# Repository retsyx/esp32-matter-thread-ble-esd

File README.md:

# Matter Over Thread End Sleepy Device With BLE Commissioning

Implements a motion sensor with an ESP32 and a BMA400 IMU - be notified when the mailman delivers your mail by attaching an accelerometer to the mailbox lid. This code puts together all the bits that seem to be required for a Matter over Thread End Sleepy Device (ESD) with BLE commissioning.

## Power Consumption

This setup seems to average 650µA at 4V from the battery when idling. Detected motion spikes power consumption considerably. The ESP32-C6's idle power draw is very high and not practical for long lived, battery powered, Matter devices.

## Requirements

* An Espressif ESP32 device with a Thread and BLE radio (for example, the ESP32-C6). If using a battery, the device should ideally have a charging circuit to allow charging the LiPo that will power the device. [The SparkFun Qwiic Pocket Development Board](https://www.sparkfun.com/products/22925) has an onboard charger, and is easy to interface with a suitable accelerometer.
* Bosch BMA400 accelerometer. The [SparkFun BMA400 Qwicc board](https://www.sparkfun.com/products/21207) interfaces easily with the SparkFun Qwiic Pocket.
* LiPo Battery. If using the linked SparkFun board, use a battery with a JST PH 2.0mm connector. Ensure that the polarity of the battery leads match the polarity of the board connector. The SparkFun Qwicc Pocket's connector polarity is the opposite of most hobby LiPos sold. Battery connector pins can be easily pried out with a utility knife to reverse their position in the connector.

### Custom Board

Alternatively, an untested custom PCB design based on the XIAO ESP32-C6 and the BMA400 accelerometer is [available](hw/board).

The LiPo Battery JST PH 2.0mm connector polarity for this board matches the typically available LiPo polarity.

## Building

* Install [esp-idf](https://docs.espressif.com/projects/esp-idf/en/stable/esp32/index.html) and [esp-matter](https://docs.espressif.com/projects/esp-matter/en/latest/esp32/)
* Set the target.
    * For the Sparkfun board use esp32-c6.
    * For the custom board, enable **Example Configuration → Use the XIAO ESP32-C6 carrier board** in (`idf.py menuconfig` (`CONFIG_BOARD_XIAO_ESP32C6=y`).
* Build the project, and flash to device

## Commissioning

With your favorite Matter commissioner (HomeKit, etc.) add the accessory.

This project uses development commissioning credentials, so the QR code is always the one below.

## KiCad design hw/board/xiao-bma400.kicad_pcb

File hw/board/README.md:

# XIAO ESP32-C6 / BMA400 Board

**This board has not been manufactured or tested.**

It is a simple board designed in KiCad.

## Manufacturing

It is a standard 2-layer, 1.6mm FR4 board. Dimensions are 40mm x 32mm.

Manufacturing files are available [here](mfr/).

An example BOM is available [here](mfr/bom.csv).

## Building the Firmware

From the repository root, set the ESP-IDF target to `esp32c6`, then enable **Example Configuration → Use the XIAO ESP32-C6 carrier board** in `idf.py menuconfig` (`CONFIG_BOARD_XIAO_ESP32C6=y`).

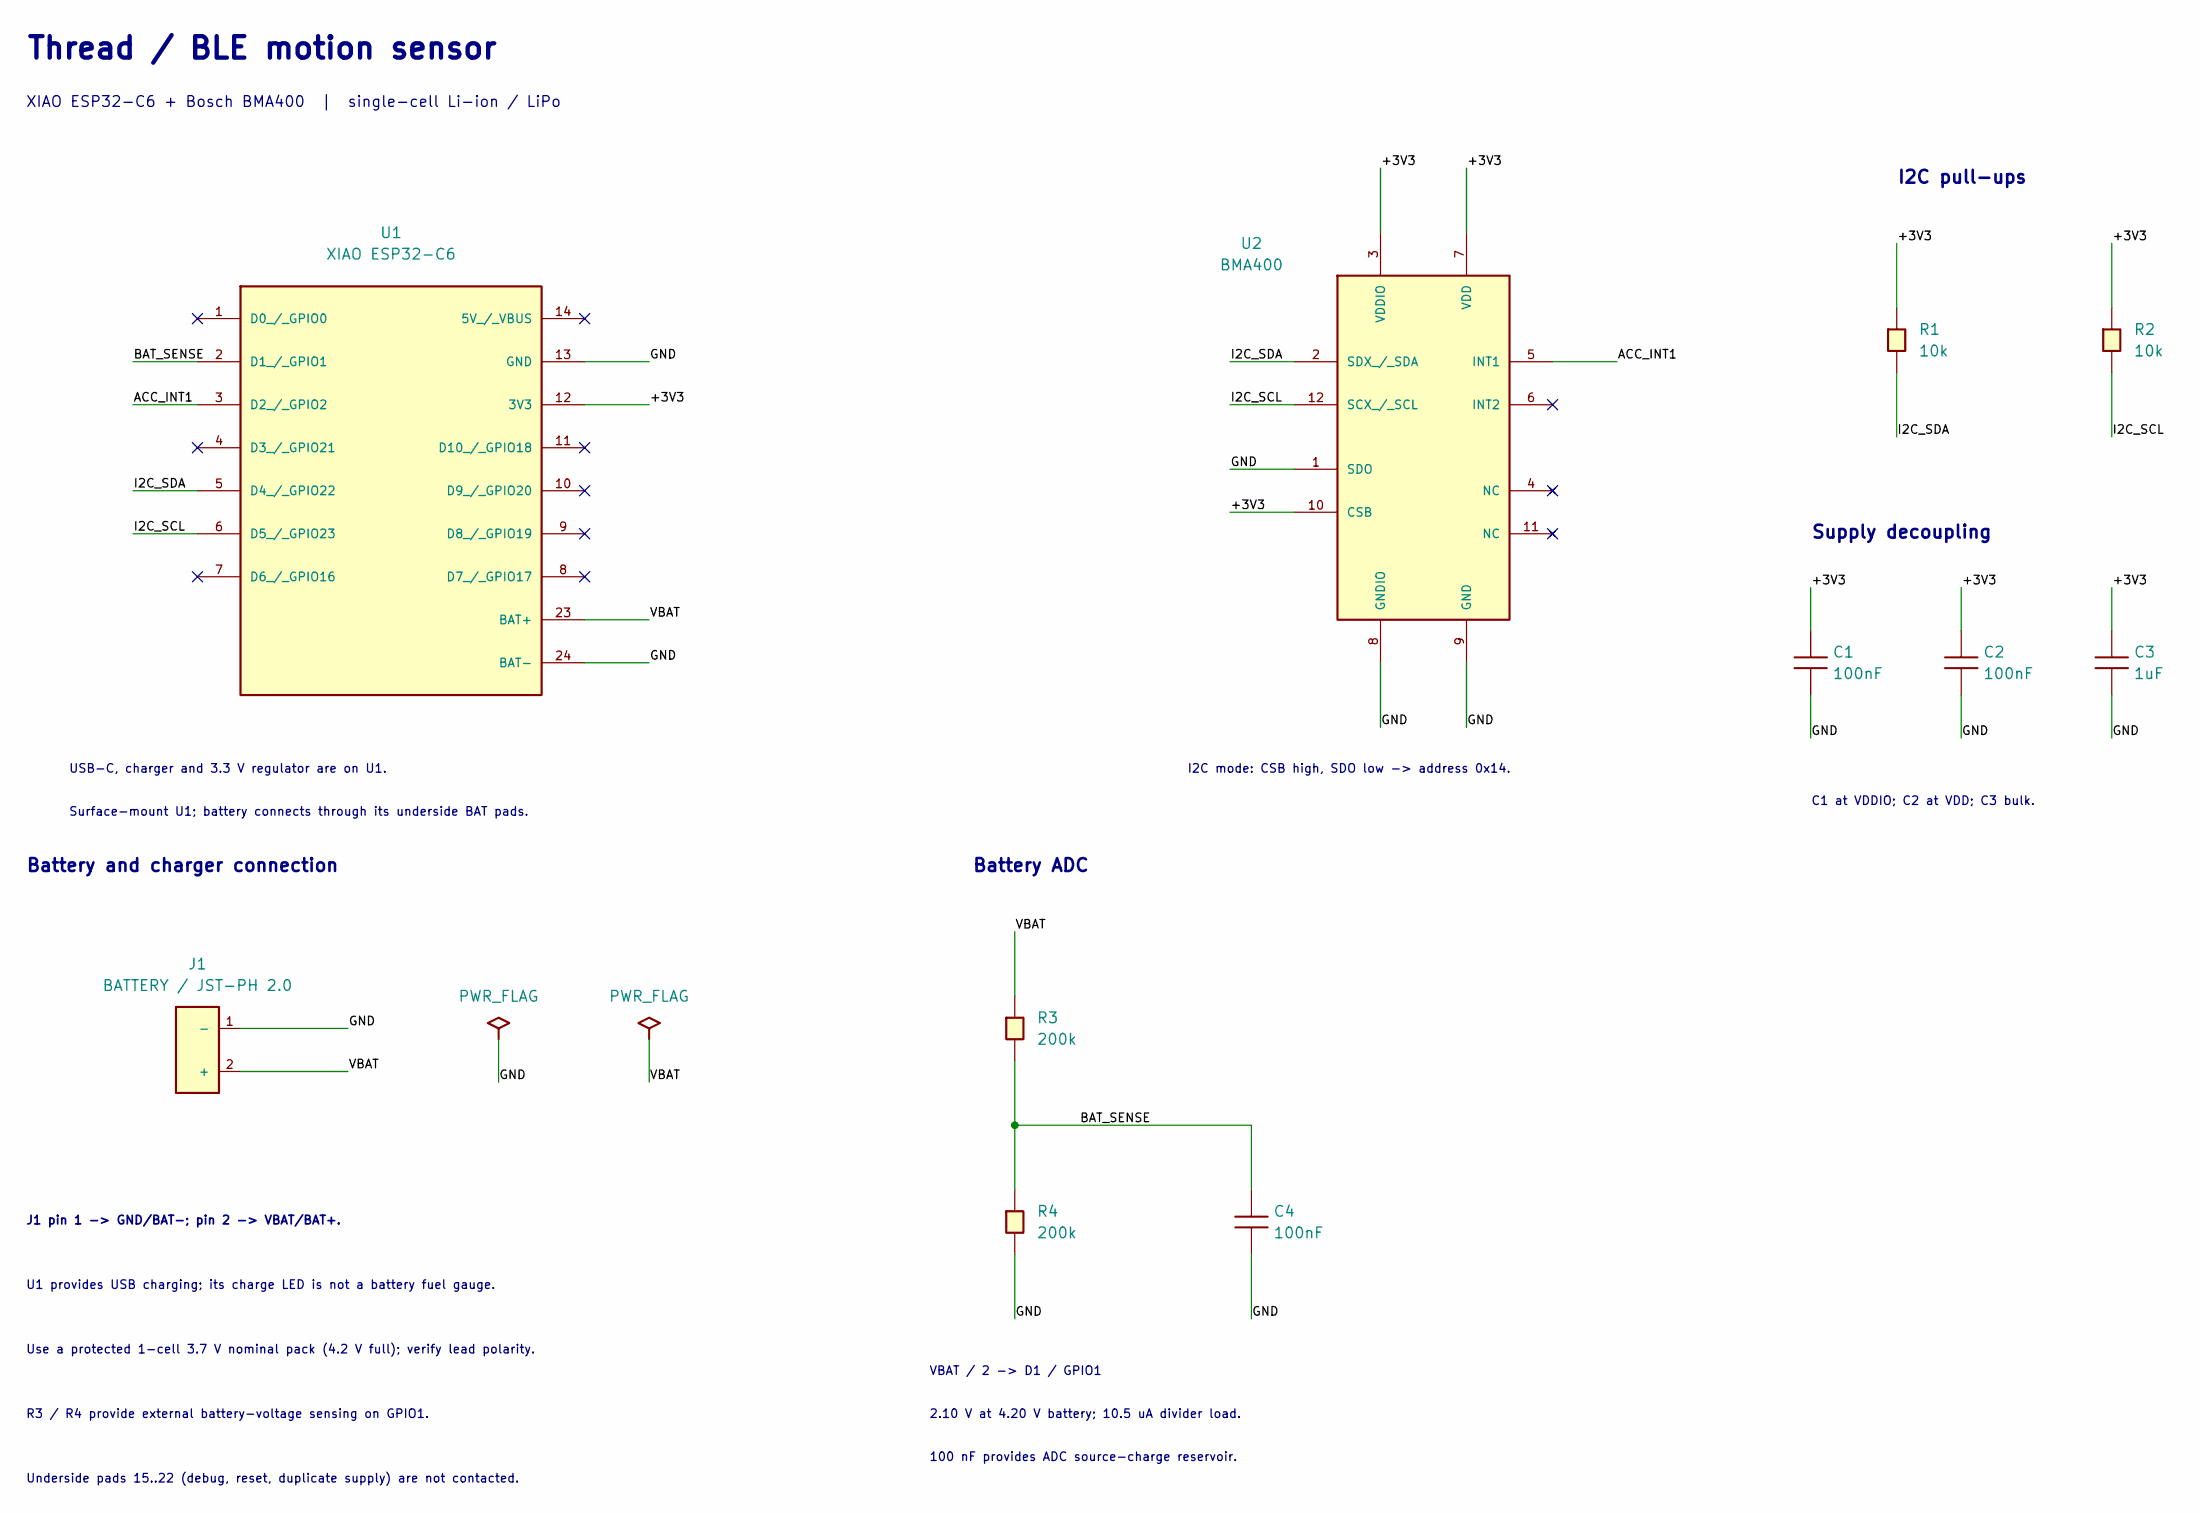
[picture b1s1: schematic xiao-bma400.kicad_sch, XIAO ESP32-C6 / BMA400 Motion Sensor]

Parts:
C1, C2, C4: 100nF; C_0603_1608Metric; Tolerance 10%; Voltage 50V; MPN C0603C104K5RACTU
C3: 1uF; C_0603_1608Metric; Tolerance 10%; Voltage 16V; MPN C0603C105K4RACTU
J1: BATTERY / JST-PH 2.0; JST_PH_S2B-PH-K_1x02_P2.00mm_Horizontal; MPN S2B-PH-K-S(LF)(SN)
R1, R2: 10k; R_0603_1608Metric; Tolerance 1%; MPN ERJ-3EKF1002V
R3, R4: 200k; R_0603_1608Metric; Tolerance 1%; MPN ERJ-3EKF2003V
U1: XIAO ESP32-C6; XIAO_ESP32C6_SMD; MPN 113991254
U2: BMA400; LGA-12_2x2mm_P0.5mm; MPN BMA400

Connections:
/+3V3: C1.1, C2.1, C3.1, R1.1, R2.1, U1.12 (3V3), U2.3 (VDDIO), U2.7 (VDD), U2.10 (CSB)
/ACC_INT1: U1.3 (D2_/_GPIO2), U2.5 (INT1)
/BAT_SENSE: C4.1, R3.2, R4.1, U1.2 (D1_/_GPIO1)
/GND: C1.2, C2.2, C3.2, C4.2, J1.1 (-), R4.2, U1.13 (GND), U1.24 (BAT-), U2.1 (SDO), U2.8 (GNDIO), U2.9 (GND)
/I2C_SCL: R2.2, U1.6 (D5_/_GPIO23), U2.12 (SCX_/_SCL)
/I2C_SDA: R1.2, U1.5 (D4_/_GPIO22), U2.2 (SDX_/_SDA)
/VBAT: J1.2 (+), R3.1, U1.23 (BAT+)

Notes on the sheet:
Battery ADC
C1 at VDDIO; C2 at VDD; C3 bulk.
Battery and charger connection
I2C mode: CSB high, SDO low -> address 0x14.
Use a protected 1-cell 3.7 V nominal pack (4.2 V full); verify lead polarity.
USB-C, charger and 3.3 V regulator are on U1.
U1 provides USB charging; its charge LED is not a battery fuel gauge.
Surface-mount U1; battery connects through its underside BAT pads.
XIAO ESP32-C6 + Bosch BMA400 | single-cell Li-ion / LiPo
Underside pads 15..22 (debug, reset, duplicate supply) are not contacted.
2.10 V at 4.20 V battery; 10.5 uA divider load.
VBAT / 2 -> D1 / GPIO1
100 nF provides ADC source-charge reservoir.
Thread / BLE motion sensor
Supply decoupling
R3 / R4 provide external battery-voltage sensing on GPIO1.
I2C pull-ups
J1 pin 1 -> GND/BAT-; pin 2 -> VBAT/BAT+.

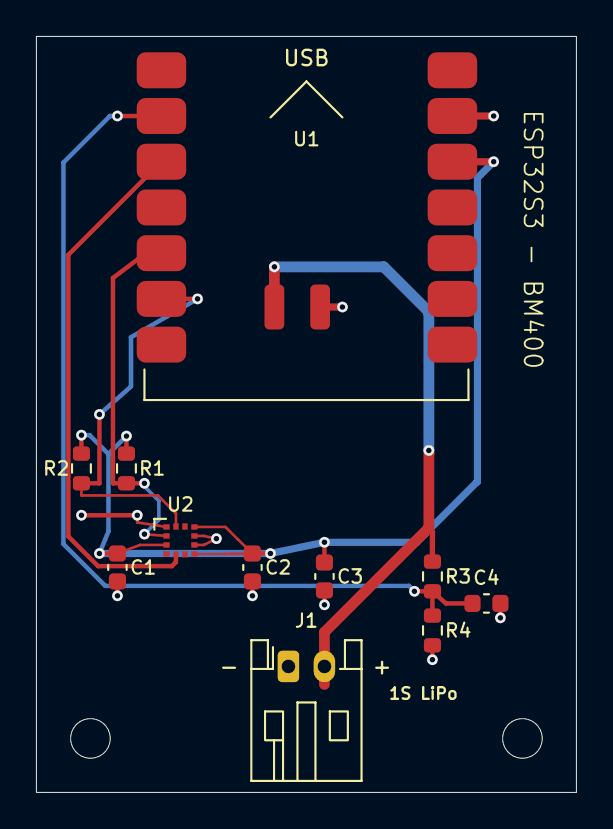
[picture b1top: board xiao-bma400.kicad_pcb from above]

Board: 2 copper layers, 30.0 x 42.0 mm, 13 parts (0 on the bottom side), 7 nets.

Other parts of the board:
H1, H2: MountingHole_2.2mm_M2
